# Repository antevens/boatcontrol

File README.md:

# Prototype, use at your own risk

# Boatcontrol

## About

Boatcontrol is an open hardware design for a marine grade SMART/IoT electrical
distribution panel and electronics platform (boat) controller.

It's an I/O breakout board capable of switching 32 onboard laching relays and
optionally 32 momentary/laching relays using addon boards switchnig  up to 60A
AC/DC 0-400V per circuit.

The "smart" part is provided by either a **Raspberry Pi** HAT or a
**Nvidia Jetson** (Nano/Xavier NX) either of which can be mounted on the board.

All critical parts are designed to be field serviceable, components using
through-holes are used where possible for better durability in mobile marine
environment. Note that these boards need to carry significant amounts of current
and high voltage and as such PCB thickness and clearances are CRITICAL along
with proper thermal management.

Special care has been taken to limit idle power consumption wherever possible, on
it's own the board will only consume 15 Milliwatts when idle, if a Raspberry Pi (RPi) Zero is
mated it will add 80-120 Milliwatts, a fully fledged RPi 4 with all the bells and
whistles will add up to 3.4 Watts, a Jetson Xavier NX will bring the total to
10-15 Watts depending on configuration. Jumpers are provided where applicable
to disable LEDs to reduce power consumption when idle. Each active indicator LED
will likely consume 10-20 Milliwatts. Note that using a momentary add-on board can increase
the power consumption substancially depending on which relays are used and how
much time they spend on the "ON" position.

Effort was taken to make the boards as reliable as possible and enable them to
be operated in emergencies and under failure conditions. All circuits can be
operated manually on the board as long as the board has a power source over 6v
and below 30v (see optional 12V vs 24V operation and PSU).
Operation using external 5V TTL inputs via the RJ45 connectors is
available regardless of the state or presence of the RPi/Jetson.

The board can be set to run in either 12V or 24V mode, for operation
over 13V please make sure the optional 12V PSU components are in place and
the appropriate solder jumpers bridged.
For 12V operation make sure the 12V bypass jumper/solder pads are bridged.

## PCB Stack & Manufacturing

The design includes a main board and (at the time of launch) two optional addon
boards, the primary board is designed for 4 layer 2.4-3.2mm PCBs with the following sizes/layers:

#### Main board - 536mm x 308mm (just over 21" x 12")
* Front Power, 6oz (220um) copper, min spacing 0.500mm)
* First Signal, 1oz (35um) copper, min spacing 0.250mm)
* Second Signal, 1oz (35um) copper, min spacing 0.250mm)
* Back Power, 6oz (220um) copper, min spacing 0.500mm)

#### Addon boards - 153mm x 106mm (just over 5" x 4")
* The high current daughter board is designed for 4 layer 1/13oz (35/450um) copper.
* The non-latching daughter board is designed for 4 layer 1/6oz (35/200um) copper.
* The non-existent current sensing daughter board .. will probably use 6oz copper.
* The non-existent Full ESD optocoupler/isolator board .. will probably use 1oz copper.

PCB Stack Thickness of daughter boards can vary as long as they are over 1mm

It's important that the power layers are on the outside for cooling purposes,
internal layers would require substantially thicker copper layers.

There aren't very many PCB manufacturers around that will/can produce a board
like this, especially in small quantities and the tooling fee will be a
substantial part of the total cost.

At the time of writing I would estimate at least $400 USD for tooling
setup and then $350 USD for each board manufactured. The manufacturers that
have online order forms for 4 layer heavy copper PCBs are:

* https://www.pcbcart.com
* https://www.pcbway.com
* https://pcbgogo.com

Note that these costs are only for the PCB, not for assembly or parts.

Note that a regular PCB panel is 457 x 610 (18" x 24"), each panel therefor can
acomidate 1 main board and 3 addon boards, consider this when ordering boards
and possibly create your own panel if your addon boards can use the same layer
stack as the primary board.

## Enclosure

Any reasonably sized enclosure will work but this board was designed to fit in
the **Fibox PC 5638 18T** (a custom mount plate will be needed since PCB standoffs don't
line up with the box attachment points).

This should give a rating of IP65/IK09

https://www.fibox.com/catalog/product/2393/2539557_ENG3.pdf

All cables should be installed with cable glands and drip loops, only install
cable glands on the bottom and optionally sides of the box, avoid making any
holes in the side facing up.

## Components, features and Bill of Materials

The components required to fully populate the board will typically cost around
{INSERT_BOM_COST}, here are full BOM carts from Mouser and DigiKey.

* {INSERT_LINK_TO_DIGIKEY}
* {INSERT_LINK_TO_MOUSER}

### Switches
Onboard switches can be momentary or locking depending on preference and application.
Typically one would use momentary switches for latching relays and locking
switches for non-latching relays.* For operating things like bilge pumps or
other devices that should only be turned on momentarily it might be beneficial
to use a non-latching relay with a momentary push button.

If for some reason locking switches are used with latching relays care must be
taken since most latching relay coils can't withstand being energized for long
periods and ideally should only be energized for less than a second*

The onboard switches are primarily for use in emergencies and debugging and while
they do provide protection against powering two coils in the same relay at the
same time they do not restrict the time a coil is energized unlike the RJ45 or
GPIO inputs.

All DPDT E3 series switches from Panasonic should work such as the ESB30 and ESB33
series, note that locking ESB30 switches can be converted to momentary
operation very easily even after soldering.

*The only exception to this would be if a user wants
to be able to physically disable a particular relay/circuit in which case two
locking relays can be used, if both of them are engaged at the same time they
will prevent all signals from reaching a latching relay behind them and at the
same time prevent each other from energizing the relay.

### Circuit breakers

The Schurter T9-818 breakers are  available in 3-15A current ratings and can
handle up to 48VDC and up to 240VAC.

The main board has a total of 32 breakers in 3 bank configurations, the board
can be outfitted with any configuration of breakers as long as the total does
not exceed 60A per bank or if a bank exceeds 60A then it should be protected by an
external 60A AC or DC breaker.

### The main (base) board layout includes sockets/circuits for:

#### 16 x 0-24V DC Common input channels/circuits:
* Input polarity protection and indicator LED
* Latching relay rated for 24V DC
* Thermally fused to 3A (can be swapped for 6A, 10A and 16A)
* Total current of these circuits should not exceed 60A

#### 8 x 0-24V DC Common input channels/circuits:
* Input polarity protection and indicator LED
* Latching relay rated for 24V DC
* 4 x thermally fused to 6A (can be swapped for 6A, 10A and 16A)
* 2 x thermally fused to 10A (can be swapped for 6A, 10A and 16A)
* 2 x thermally fused to 16A (can be swapped for 6A, 10A and 16A)
* Total current of these circuits should not exceed 60A

#### 8 x 100-250V AC Common input channels/circuits:
* AC Live/Neutral indicator LED
* Latching relay rated for 24V DC
* 4 x thermally fused to 6A (can be swapped for 6A, 10A and 16A)
* 2 x thermally fused to 10A (can be swapped for 6A, 10A and 16A)
* 2 x thermally fused to 16A (can be swapped for 6A, 10A and 16A)
* Total current of these circuits should not exceed 60A

## Addon boards
Addon boards connect to the main board using a 2 x 20 female pin header.
The main board male connectors are reversed compared to the GPIO header to avoid
confusion and prevent RPis or Jetson boards from being accidentally connected to
an addon-board header.

### Latching Relay Addon Board:
* 8 x 0-277V AC/DC Individual input/output channels/circuits
* Individual channel current should not exceed 60A
* No circuit breakers, polarity indicators or protection

### Momentary (Non Latching) Paired Addon Board:
* 16 (8 pairs*) x 12V DC non latching input/output channels/circuits
* Individual channel current should not exceed 32A
* No circuit breakers, polarity indicators or protection

_Non-latching Relays are paired and only one of a pair can be powered at any given time._

_All relays on a board share a common "Anode"/"Cathode", make sure to
adjust the solder-jumpers on the backside for the type of relays used so that
the relay polarity is correct. and that the correct driver array is chosen
(ULN2803A vs. TBD62783APG)_

Keep in mind that there is no requirement to fully populate the board and a partially
populated board is a great way to plan for future expansions given that the
board is field serviceable assuming the heavy copper soldering is done.

## Modes of operation
Each channel/circuit can be controlled using three different methods:

1. Using the onboard switches (these directly energize the relay coils)

2. Using two external switch signals wired up using CAT5/6 with RJ45
connectors. The signals use 5V TTL logic and are active HIGH.
The signals are filtered for noise and duration to protect the relays,
this ensures that only one coil can be energized at any given time and
only for a period of 1 second. Due to this filtering these can be safely
wired to 3-way "Latching" wall/panel switches or momentary push buttons.

3. Using I2C via the 2x20 Header, typically this would be done using a
Raspberry Pi (RPi) or Nvidia Jetson, for power efficiency consider using a RPi Zero.
See Node-Red source for IoT web based interfaces that can run on these platforms.

* Onboard bi-colour LEDs indicate coil energy state and pulses to "ON"/"OFF" coils.
* For latching relays RED indicates the circuit being turned ON while GREEN indicates the circuit being turned OFF.
* For non-latching relays RED and GREEN each represent a separate relay in a pair.

## Technical details

While the scale is disproportionate the main board is really just a rather large
Raspberry Pi HAT though it does not require an RPi to operate.
__Note that the board will act as a power supply for the RPi and Jetson
Nano eliminating the need for a separate PSU.__
__The Nvidia JetsonXavier products such as the NX and AGX will still need a separate (19V)
power source.__

All communication between the RPi and the board is done using I2C, this only
requires 2 pins/wires and makes it safe to use in combination with most if not all
other HATs. In particular it can co-exist with AIS and GPS hats like the dAISy though you
might want to run your chart-plotting or navigation software on a separate
RPi/Jetson NX and have a dedicated micro-computer for controlling your electrical system.

The Sailor Hat or PICAN-M HATs might be of particular interest to allow the
Boatcontrol board to act as an NMEA 0183/2000 or Seatalk device.

* https://hatlabs.fi/product-category/sh-rpi/sh-rpi-devices
* https://www.skpang.co.uk/collections/hats/products/pican-m-with-can-bus-micro-c-and-rs422-connector-3a-smps
* https://copperhilltech.com/pican-m-nmea-0183-nmea-2000-hat-for-raspberry-pi/

### RJ45 Connectors & Remote I/O
The top/right (J108) RJ45 connector is used to remotely control relays on the main
board. Each RJ45 socket controls 2 latching relays or 2 non-latching relay pairs (4).
Every socket consists of 4 separate 5V supply pins supplied via a 10KΩ resistor.

All J108 (top connector)inputs are ESD protected using clamp diodes in the
74HCT86 packs to the following standards:
* HBM JESD22-A114F exceeds 2000 V
* MM JESD22-A115-A exceeds 200 V

For long cable runs the resistor banks on the back can be replaced with lower
resistance values.

Half of the bottom/left (J107) RJ45 connector is used to remotely control addon
boards.

Each RJ45 socket can control 4 channels, typically controlling 2 latching relays
or 2 non-latching relay pairs (4).

**Note that for these connectors there are no current limiting resistors so
current is only limited by what the onboard PSU can supply and shorting this
can de-power the RPi/Jetson!**

**Pairing is important for all RJ45CAT5/6 wiring, it's highly
recommended that the source/sink to control each relay uses a twisted pair,
this will minimize loss and interference. Pairs are typically colored as shown here**

_Advanced uses may also include shielding but this is beyond the scope of this document._

#### 12V "High Voltage/Current" Pins
There are 16 extra IO pins that can provide up to 500mA each, this is provided
using an MCP23017 and a ULN2803* with a clamp diode. Examples of use cases would
be external relays, solenoids, small motors, high power LEDs, Cameras, etc.

_*can be substituted with a TBD62783APG to swap polarity from 12V source to GND
sink._

#### Raspberry Pi / Jetson  I/O
All pins from the GPIO header are made available via RJ45 to allow easy
expansion and remote mounting of devices such as GPS and AIS devices.

_Note that the 5V pins are shared with the RPi and maximum currents governed by
the RPi design not the Boatcontrol._

*_Note that no additional protection or filtering is provided, the pins are
simply mapped from the RPi GPIO header directly to RJ45 without any provision
to minimize signal degradation or distortion._

_Note that this includes the I2C bus which can be used to communicate directly
with all devices on the main and addon boards_

**IMPORTANT** - Since no extra ESD filtering or opto-isolaion is provided for
thes GPIO ports if there there is any chance of surges or high voltages these
should be isolated from the board using digital isolators or optocouplers
and transient voltage suppressors. For remote installations of the
Raspberry Pi/Jetson you might also want to add debounce and provide 3v from an
isolated source.

### RPi HAT / Jetson GPIO Interface
Using the GPIO header there are two ways to connect an RPi or Nvidia Jetson
device to the board.
1. Install female pin header on the Boatcontrol, mount the device directly in
the upside down position, if you choose this option make sure the particular board you are mounting has
enough clearance.*
2. Install a male pin header on the Boatcontrol, mount the device using a
   ribbon cable.

*While the RPi Zero is guaranteed to fit and with long headers all the
Pi/Pi2/Pi2/Pi4s should fit you should make sure your device fits before
choosing this mounting method.

_If using a Jetson Xavier NX or AGX make sure you use the horizontal inductors for the
PSU since the vertical arrangement can block one of the mounting holes._

### Addon cards

### I2C interface and addresses
The I2C addresses of the IO Expanders can be modified* using solder jumpers on
the backside of the PCB but the defaults are:

    0x20 (32) 3A Common Input DC #1-8
    0x21 (33) 3A Common Input DC #9-16
    0x22 (34) 6/10/16A Common Input DC
    0x23 (35) 6/10/16A Common Input AC
    0x24 (36) 60A Individual AC/DC
    0x25 (37) Additional IO #1 to RJ45 Cat5/6
    0x26 (38) Additional IO #2 to RJ45 Cat5/6

*Bring plenty of watts, it's a 6oz PCB!

# Software
One of the primary advantages of having the GPIO interface and using a
Raspberry Pi or Nvidia Jetson to interface with the board is the simplicity and
ease of use allowing each installation to be customized for the particular boat
and users, changes can be made in real-time using a web browser and all the
functionality and features are accessible from any web enabled device onboard
or remote.

The following are screenshots from development UIs used to debug and test the
hardware, they show some of the functionality that's possible including
day/night views, automated alerts and functionality.

This particular interface is built using Node-Red and is running on an RPi 4.

# Open Hardware

Feel free to modify this to suit your own needs or have it made as it's
currently configured. Be careful when upgrading circuit breakers to not exceed the
current/thermal capacity of the board. If you use thinner copper than 6oz make
sure to appropriately downgrade the thermal breakers to reduce maximum current.

## Bus bars, jumper wires and 2 layer boards

Depending on where you live and your requirements it might make more sense
for you to use laser cut copper bus bars or solder wires on the back of your PCB to
avoid the expensive 6oz copper layers.

The PCB was architected to facilitate 1oz / 2 layer construction, there is a
git branch called [2layer](../../tree/2layers) which is the last version supporting 2 layers. *In
theory* this could be made with 1oz copper and used with bus bars or jumper
wires but it's not been kept up to date. Let me know if you want to use this
and we can probably work together to merge relevant changes.

## Key design decisions and parameters

* All critical components are through-hole for field maintenance on moving platforms and secure attachment for vibration and G loads.
* All relays can be controlled from either the RPi/Nvidia or using analog control signals via RJ45/CAT5/6 connectors/cables.
* All onboard relays are latching dual coil with individual control circuits.
* All analog input channels have pulse generators for the relays to protect them from overheating.
* Built-in high efficiency 5/12v step down converters to power the RPi/Nano and logic components and supply current for analog control.
* 8x 3-16A 250V AC shared bus protected circuits
* 24x 3-16A 12-24V DC shared bus protected circuits
* 32x 12-24V 500mA DC Logic/Relay breakout via RJ45
* Optional 16x 250V AC non-latching unprotected add-on board
* Optional 8x 60A 277V AC latching individual unprotected add-on board
* All onboard DC channels are polarity protected with high efficiency PFETs
* Protection is provided using thermal circuit breakers, the permitted amperage can be changed by switching out breakers, no breakers are provided for the 60A circuits, suggest using external breakers.

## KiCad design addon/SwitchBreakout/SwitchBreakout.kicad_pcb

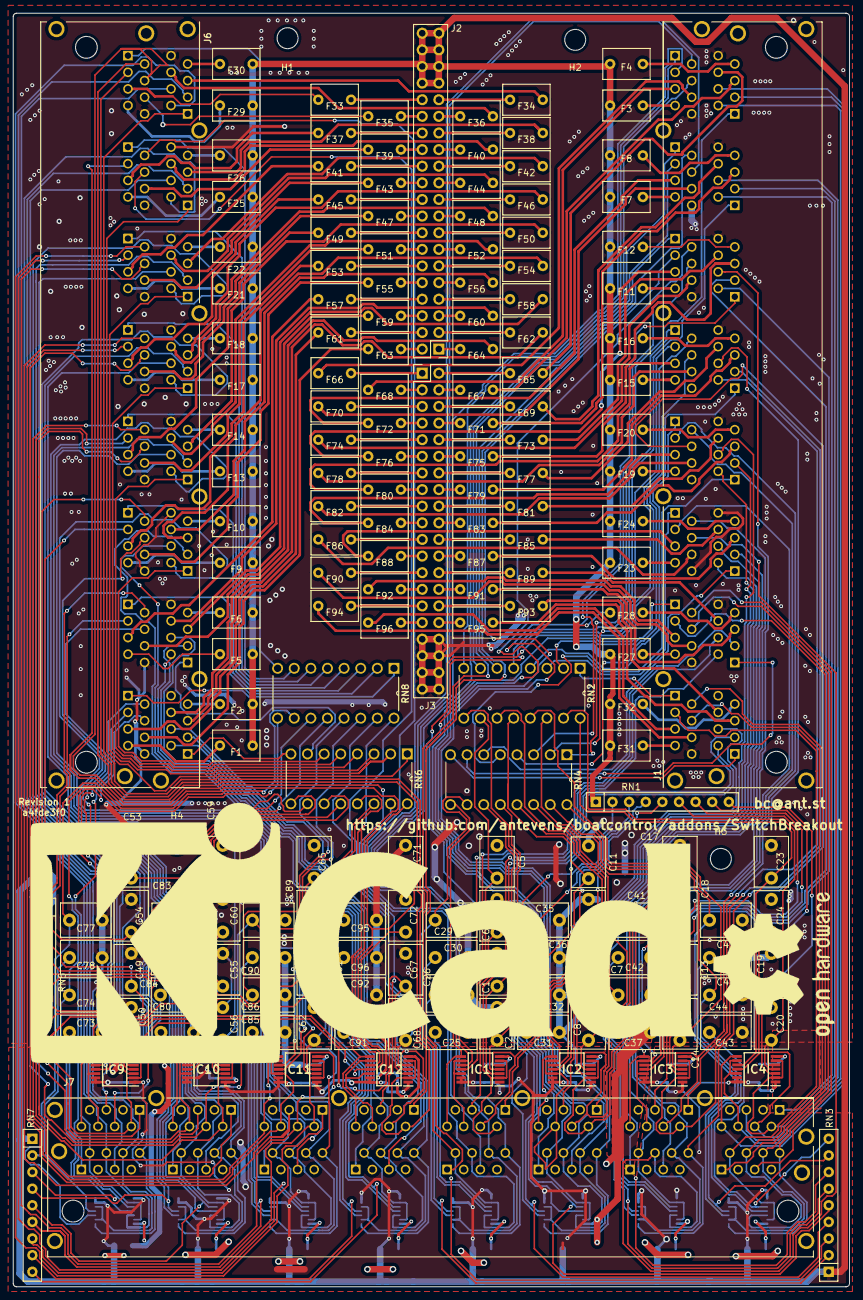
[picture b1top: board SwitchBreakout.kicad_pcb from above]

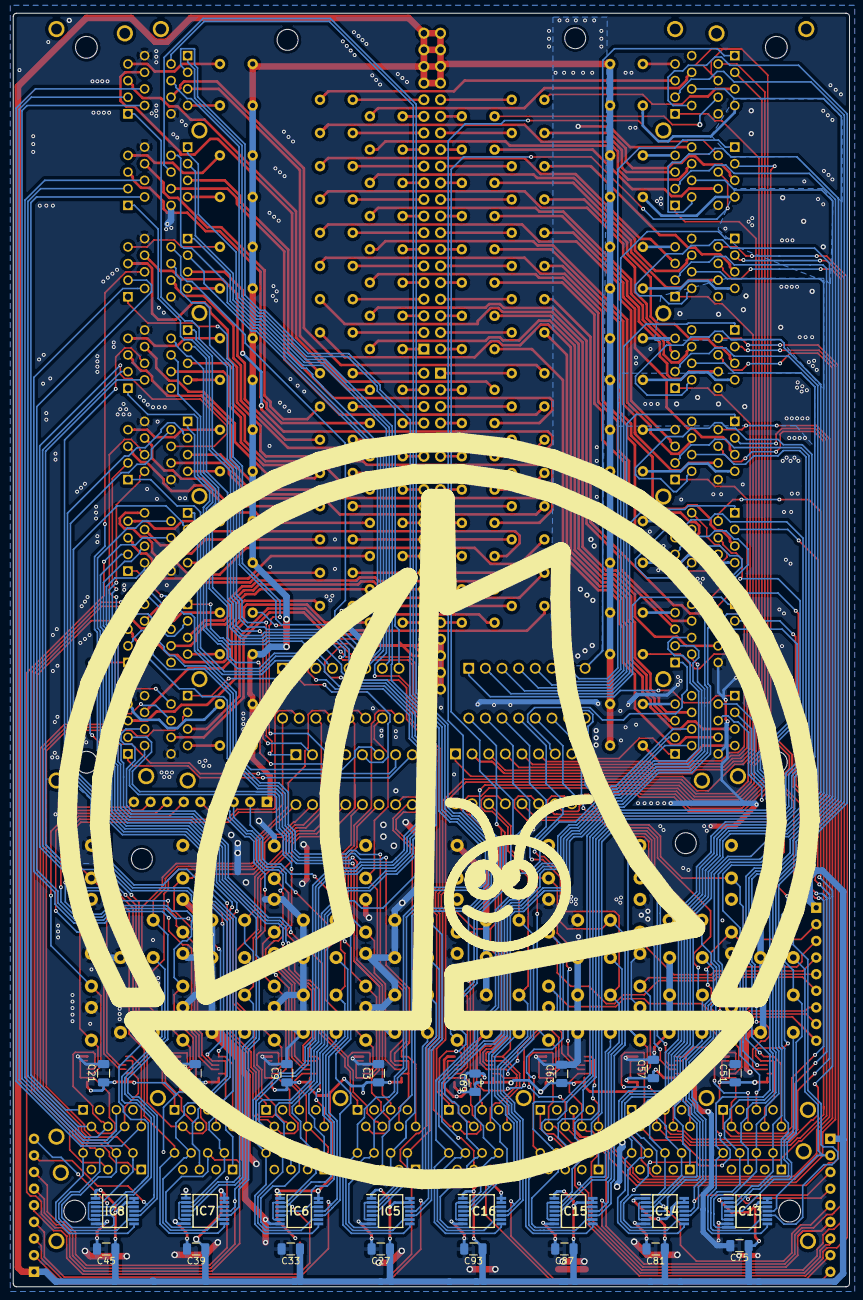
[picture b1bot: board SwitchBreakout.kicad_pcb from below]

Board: 2 copper layers, 127.8 x 194.6 mm, 213 parts (26 on the bottom side), 354 nets.

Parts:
C1, C2, C5, C6, C7, C8, C11, C12, C13, C14, C17, C18, C19, C20, C23, C24, C25, C26, C29, C30, C31, C32, C35, C36, C37, C38, C41, C42, C43, C44, C47, C48, C49, C50, C53, C54, C55, C56, C59, C60, C61, C62, C65, C66, C67, C68, C71, C72, C73, C74, C77, C78, C79, C80, C83, C84, C85, C86, C89, C90, C91, C92, C95, C96: 1uF; C_Disc_D7.5mm_W5.0mm_P5.00mm
C3, C9, C15, C21, C27, C33, C39, C45, C51, C57, C63, C69, C75, C81, C87, C93: 0.1uF; C_1206_3216Metric
F1, F2, F3, F4, F5, F6, F7, F8, F9, F10, F11, F12, F13, F14, F15, F16, F17, F18, F19, F20, F21, F22, F23, F24, F25, F26, F27, F28, F29, F30, F31, F32, F33, F34, F35, F36, F37, F38, F39, F40, F41, F42, F43, F44, F45, F46, F47, F48, F49, F50, F51, F52, F53, F54, F55, F56, F57, F58, F59, F60, F61, F62, F63, F64, F65, F66, F67, F68, F69, F70, F71, F72, F73, F74, F75, F76, F77, F78, F79, F80, F81, F82, F83, F84, F85, F86, F87, F88, F89, F90, F91, F92, F93, F94, F95, F96: Polyfuse; C_Rect_L7.0mm_W4.5mm_P5.00mm
G1: LOGO_ANT; Ant_Logo_SilkScreen
G2: LOGO_RUGLUDALLUR; Rugludallur-Logo_SilkScreen
H1, H2, H3, H4: MountingHole; MountingHole_3.2mm_M3
IC1, IC2, IC3, IC4, IC5, IC6, IC7, IC8, IC9, IC10, IC11, IC12, IC13, IC14, IC15, IC16: SN74HCS72QPWRQ1; SOP65P640X120-14N
J1, J6, J7: SS73100-047F; STEWART_SS73100-047F
J2, J3: Conn_02x20_Odd_Even; PinHeader_2x20_P2.54mm_Vertical
LOGO1: Logo_Open_Hardware_Large; OSHW-Logo2_24.3x20mm_SilkScreen
LOGO2: Logo_Open_Hardware_Large; KiCad-Logo_40mm_SilkScreen
RN1, RN3, RN5, RN7: 100KΩ; R_Array_SIP9
RN2, RN4, RN6, RN8: 1KΩ; DIP254P762X432-16P

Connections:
/A1: J1.A_2, J7.P_1
/A2: IC8.2, IC8.6, J1.A_3, J7.P_2
/A4: IC8.5, J1.A_4, J7.P_4
/A5: J1.B_2, J7.P_5
/A6: IC8.9, IC8.12, J1.B_3, J7.P_6
/A8: IC8.8, J1.B_4, J7.P_8
/B1: J1.C_2, J7.O_1
/B2: IC7.2, IC7.6, J1.C_3, J7.O_2
/B4: IC7.5, J1.C_4, J7.O_4
/B5: J1.D_2, J7.O_5
/B6: IC7.9, IC7.12, J1.D_3, J7.O_6
/B8: IC7.8, J1.D_4, J7.O_8
/C1: J1.E_2, J7.N_1
/C2: IC6.2, IC6.6, J1.E_3, J7.N_2
/C4: IC6.5, J1.E_4, J7.N_4
/C5: J1.F_2, J7.N_5
/C6: IC6.9, IC6.12, J1.F_3, J7.N_6
/C8: IC6.8, J1.F_4, J7.N_8
/D1: J1.G_2, J7.M_1
/D2: IC5.2, IC5.6, J1.G_3, J7.M_2
/D4: IC5.5, J1.G_4, J7.M_4
/D5: J1.H_2, J7.M_5
/D6: IC5.9, IC5.12, J1.H_3, J7.M_6
/D8: IC5.8, J1.H_4, J7.M_8
/D-Lach 9-16/BTN1: J1.I_1, RN4.8
/D-Lach 9-16/BTN2: J1.J_1, RN4.7
/D-Lach 9-16/BTN3: J1.K_1, RN4.6
/D-Lach 9-16/BTN4: J1.L_1, RN4.5
/D-Lach 9-16/BTN5: J1.M_1, RN4.4
/D-Lach 9-16/BTN6: J1.N_1, RN4.3
/D-Lach 9-16/BTN7: J1.O_1, RN4.2
/D-Lach 9-16/BTN8: J1.P_1, RN4.1
/D-Lach 9-16/D-Latch 0/BTN1: C26.2, IC5.4, RN4.9
/D-Lach 9-16/D-Latch 0/BTN2: C29.2, IC5.10, RN4.10
/D-Lach 9-16/D-Latch 0/CLK1: C25.2, IC5.3, RN3.3
/D-Lach 9-16/D-Latch 0/CLK2: C30.2, IC5.11, RN3.2
/D-Lach 9-16/D-Latch 1/BTN1: C32.2, IC6.4, RN4.11
/D-Lach 9-16/D-Latch 1/BTN2: C35.2, IC6.10, RN4.12
/D-Lach 9-16/D-Latch 1/CLK1: C31.2, IC6.3, RN3.5
/D-Lach 9-16/D-Latch 1/CLK2: C36.2, IC6.11, RN3.4
/D-Lach 9-16/D-Latch 2/BTN1: C38.2, IC7.4, RN4.13
/D-Lach 9-16/D-Latch 2/BTN2: C41.2, IC7.10, RN4.14
/D-Lach 9-16/D-Latch 2/CLK1: C37.2, IC7.3, RN3.7
/D-Lach 9-16/D-Latch 2/CLK2: C42.2, IC7.11, RN3.6
/D-Lach 9-16/D-Latch 4/BTN1: C44.2, IC8.4, RN4.15
/D-Lach 9-16/D-Latch 4/BTN2: C47.2, IC8.10, RN4.16
/D-Lach 9-16/D-Latch 4/CLK1: C43.2, IC8.3, RN3.9
/D-Lach 9-16/D-Latch 4/CLK2: C48.2, IC8.11, RN3.8
/D-Latch 1-8/BTN1: J1.H_1, RN2.8
/D-Latch 1-8/BTN2: J1.G_1, RN2.7
/D-Latch 1-8/BTN3: J1.F_1, RN2.6
/D-Latch 1-8/BTN4: J1.E_1, RN2.5
/D-Latch 1-8/BTN5: J1.D_1, RN2.4
/D-Latch 1-8/BTN6: J1.C_1, RN2.3
/D-Latch 1-8/BTN7: J1.B_1, RN2.2
/D-Latch 1-8/BTN8: J1.A_1, RN2.1
/D-Latch 1-8/D-Latch 0/BTN1: C2.2, IC1.4, RN2.9
/D-Latch 1-8/D-Latch 0/BTN2: C5.2, IC1.10, RN2.10
/D-Latch 1-8/D-Latch 0/CLK1: C1.2, IC1.3, RN1.3
/D-Latch 1-8/D-Latch 0/CLK2: C6.2, IC1.11, RN1.2
/D-Latch 1-8/D-Latch 1/BTN1: C8.2, IC2.4, RN2.11
/D-Latch 1-8/D-Latch 1/BTN2: C11.2, IC2.10, RN2.12
/D-Latch 1-8/D-Latch 1/CLK1: C7.2, IC2.3, RN1.5
/D-Latch 1-8/D-Latch 1/CLK2: C12.2, IC2.11, RN1.4
/D-Latch 1-8/D-Latch 2/BTN1: C14.2, IC3.4, RN2.13
/D-Latch 1-8/D-Latch 2/BTN2: C17.2, IC3.10, RN2.14
/D-Latch 1-8/D-Latch 2/CLK1: C13.2, IC3.3, RN1.7
/D-Latch 1-8/D-Latch 2/CLK2: C18.2, IC3.11, RN1.6
/D-Latch 1-8/D-Latch 4/BTN1: C20.2, IC4.4, RN2.15
/D-Latch 1-8/D-Latch 4/BTN2: C23.2, IC4.10, RN2.16
/D-Latch 1-8/D-Latch 4/CLK1: C19.2, IC4.3, RN1.9
/D-Latch 1-8/D-Latch 4/CLK2: C24.2, IC4.11, RN1.8
/D-Latch 17-24/BTN1: J6.H_1, RN6.8
/D-Latch 17-24/BTN2: J6.G_1, RN6.7
/D-Latch 17-24/BTN3: J6.F_1, RN6.6
/D-Latch 17-24/BTN4: J6.E_1, RN6.5
/D-Latch 17-24/BTN5: J6.D_1, RN6.4
/D-Latch 17-24/BTN6: J6.C_1, RN6.3
/D-Latch 17-24/BTN7: J6.B_1, RN6.2
/D-Latch 17-24/BTN8: J6.A_1, RN6.1
/D-Latch 17-24/D-Latch 0/BTN1: C50.2, IC9.4, RN6.9
/D-Latch 17-24/D-Latch 0/BTN2: C53.2, IC9.10, RN6.10
/D-Latch 17-24/D-Latch 0/CLK1: C49.2, IC9.3, RN5.3
/D-Latch 17-24/D-Latch 0/CLK2: C54.2, IC9.11, RN5.2
/D-Latch 17-24/D-Latch 1/BTN1: C56.2, IC10.4, RN6.11
/D-Latch 17-24/D-Latch 1/BTN2: C59.2, IC10.10, RN6.12
/D-Latch 17-24/D-Latch 1/CLK1: C55.2, IC10.3, RN5.5
/D-Latch 17-24/D-Latch 1/CLK2: C60.2, IC10.11, RN5.4
/D-Latch 17-24/D-Latch 2/BTN1: C62.2, IC11.4, RN6.13
/D-Latch 17-24/D-Latch 2/BTN2: C65.2, IC11.10, RN6.14
/D-Latch 17-24/D-Latch 2/CLK1: C61.2, IC11.3, RN5.7
/D-Latch 17-24/D-Latch 2/CLK2: C66.2, IC11.11, RN5.6
/D-Latch 17-24/D-Latch 4/BTN1: C68.2, IC12.4, RN6.15
/D-Latch 17-24/D-Latch 4/BTN2: C71.2, IC12.10, RN6.16
/D-Latch 17-24/D-Latch 4/CLK1: C67.2, IC12.3, RN5.9
/D-Latch 17-24/D-Latch 4/CLK2: C72.2, IC12.11, RN5.8
/D-Latch 25-32/BTN1: J6.I_1, RN8.8
/D-Latch 25-32/BTN2: J6.J_1, RN8.7
/D-Latch 25-32/BTN3: J6.K_1, RN8.6
/D-Latch 25-32/BTN4: J6.L_1, RN8.5
/D-Latch 25-32/BTN5: J6.M_1, RN8.4
/D-Latch 25-32/BTN6: J6.N_1, RN8.3
/D-Latch 25-32/BTN7: J6.O_1, RN8.2
/D-Latch 25-32/BTN8: J6.P_1, RN8.1
/D-Latch 25-32/D-Latch 0/BTN1: C74.2, IC13.4, RN8.9
/D-Latch 25-32/D-Latch 0/BTN2: C77.2, IC13.10, RN8.10
/D-Latch 25-32/D-Latch 0/CLK1: C73.2, IC13.3, RN7.3
/D-Latch 25-32/D-Latch 0/CLK2: C78.2, IC13.11, RN7.2
/D-Latch 25-32/D-Latch 1/BTN1: C80.2, IC14.4, RN8.11
/D-Latch 25-32/D-Latch 1/BTN2: C83.2, IC14.10, RN8.12
/D-Latch 25-32/D-Latch 1/CLK1: C79.2, IC14.3, RN7.5
/D-Latch 25-32/D-Latch 1/CLK2: C84.2, IC14.11, RN7.4
/D-Latch 25-32/D-Latch 2/BTN1: C86.2, IC15.4, RN8.13
/D-Latch 25-32/D-Latch 2/BTN2: C89.2, IC15.10, RN8.14
/D-Latch 25-32/D-Latch 2/CLK1: C85.2, IC15.3, RN7.7
/D-Latch 25-32/D-Latch 2/CLK2: C90.2, IC15.11, RN7.6
/D-Latch 25-32/D-Latch 4/BTN1: C92.2, IC16.4, RN8.15
/D-Latch 25-32/D-Latch 4/BTN2: C95.2, IC16.10, RN8.16
/D-Latch 25-32/D-Latch 4/CLK1: C91.2, IC16.3, RN7.9
/D-Latch 25-32/D-Latch 4/CLK2: C96.2, IC16.11, RN7.8
/E1: J1.I_2, J7.E_1
/E2: IC1.2, IC1.6, J1.I_3, J7.E_2
/E4: IC1.5, J1.I_4, J7.E_4
/E5: J1.J_2, J7.E_5
/E6: IC1.9, IC1.12, J1.J_3, J7.E_6
/E8: IC1.8, J1.J_4, J7.E_8
/F1: J1.K_2, J7.F_1
/F2: IC2.2, IC2.6, J1.K_3, J7.F_2
/F4: IC2.5, J1.K_4, J7.F_4
/F5: J1.L_2, J7.F_5
/F6: IC2.9, IC2.12, J1.L_3, J7.F_6
/F8: IC2.8, J1.L_4, J7.F_8
/G1: J1.M_2, J7.G_1
/G2: IC3.2, IC3.6, J1.M_3, J7.G_2
/G4: IC3.5, J1.M_4, J7.G_4
/G5: J1.N_2, J7.G_5
/G6: IC3.9, IC3.12, J1.N_3, J7.G_6
/G8: IC3.8, J1.N_4, J7.G_8
/H1: J1.O_2, J7.H_1
/H2: IC4.2, IC4.6, J1.O_3, J7.H_2
/H4: IC4.5, J1.O_4, J7.H_4
/H5: J1.P_2, J7.H_5
/H6: IC4.9, IC4.12, J1.P_3, J7.H_6
/H8: IC4.8, J1.P_4, J7.H_8
/I1: J6.A_2, J7.I_1
/I2: IC13.2, IC13.6, J6.A_3, J7.I_2
/I4: IC13.5, J6.A_4, J7.I_4
/I5: J6.B_2, J7.I_5
/I6: IC13.9, IC13.12, J6.B_3, J7.I_6
/I8: IC13.8, J6.B_4, J7.I_8
/J1: J6.C_2, J7.J_1
/J2: IC14.2, IC14.6, J6.C_3, J7.J_2
/J4: IC14.5, J6.C_4, J7.J_4
/J5: J6.D_2, J7.J_5
/J6: IC14.9, IC14.12, J6.D_3, J7.J_6
/J8: IC14.8, J6.D_4, J7.J_8
/K1: J6.E_2, J7.K_1
/K2: IC15.2, IC15.6, J6.E_3, J7.K_2
/K4: IC15.5, J6.E_4, J7.K_4
/K5: J6.F_2, J7.K_5
/K6: IC15.9, IC15.12, J6.F_3, J7.K_6
/K8: IC15.8, J6.F_4, J7.K_8
/L1: J6.G_2, J7.L_1
/L2: IC16.2, IC16.6, J6.G_3, J7.L_2
/L4: IC16.5, J6.G_4, J7.L_4
/L5: J6.H_2, J7.L_5
/L6: IC16.9, IC16.12, J6.H_3, J7.L_6
/L8: IC16.8, J6.H_4, J7.L_8
/M1: J6.I_2, J7.D_1
/M2: IC12.2, IC12.6, J6.I_3, J7.D_2
/M4: IC12.5, J6.I_4, J7.D_4
/M5: J6.J_2, J7.D_5
/M6: IC12.9, IC12.12, J6.J_3, J7.D_6
/M8: IC12.8, J6.J_4, J7.D_8
/N1: J6.K_2, J7.C_1
/N2: IC11.2, IC11.6, J6.K_3, J7.C_2
/N4: IC11.5, J6.K_4, J7.C_4
/N5: J6.L_2, J7.C_5
/N6: IC11.9, IC11.12, J6.L_3, J7.C_6
/N8: IC11.8, J6.L_4, J7.C_8
/O1: J6.M_2, J7.B_1
/O2: IC10.2, IC10.6, J6.M_3, J7.B_2
/O4: IC10.5, J6.M_4, J7.B_4
/O5: J6.N_2, J7.B_5
/O6: IC10.9, IC10.12, J6.N_3, J7.B_6
/O8: IC10.8, J6.N_4, J7.B_8
/P1: J6.O_2, J7.A_1
/P2: IC9.2, IC9.6, J6.O_3, J7.A_2
/P4: IC9.5, J6.O_4, J7.A_4
/P5: J6.P_2, J7.A_5
/P6: IC9.9, IC9.12, J6.P_3, J7.A_6
/P8: IC9.8, J6.P_4, J7.A_8
GND: C1.1, C2.1, C3.2, C5.1, C6.1, C7.1, C8.1, C9.2, C11.1, C12.1, C13.1, C14.1, C15.2, C17.1, C18.1, C19.1, C20.1, C21.2, C23.1, C24.1, C25.1, C26.1, C27.2, C29.1, C30.1, C31.1, C32.1, C33.2, C35.1, C36.1, C37.1, C38.1, C39.2, C41.1, C42.1, C43.1, C44.1, C45.2, C47.1, C48.1, C49.1, C50.1, C51.2, C53.1, C54.1, C55.1, C56.1, C57.2, C59.1, C60.1, C61.1, C62.1, C63.2, C65.1, C66.1, C67.1, C68.1, C69.2, C71.1, C72.1, C73.1, C74.1, C75.2, C77.1, C78.1, C79.1, C80.1, C81.2, C83.1, C84.1, C85.1, C86.1, C87.2, C89.1, C90.1, C91.1, C92.1, C93.2, C95.1, C96.1, IC1.7, IC2.7, IC3.7, IC4.7, IC5.7, IC6.7, IC7.7, IC8.7, IC9.7, IC10.7, IC11.7, IC12.7, IC13.7, IC14.7, IC15.7, IC16.7, J1.A_8, J1.B_8, J1.C_8, J1.D_8, J1.E_8, J1.F_8, J1.G_8, J1.H_8, J1.I_8, J1.J_8, J1.K_8, J1.L_8, J1.M_8, J1.N_8, J1.O_8, J1.P_8, J3.33, J3.34, J3.35, J3.36, J3.37, J3.38, J3.39, J3.40, J6.A_8, J6.B_8, J6.C_8, J6.D_8, J6.E_8, J6.F_8, J6.G_8, J6.H_8, J6.I_8, J6.J_8, J6.K_8, J6.L_8, J6.M_8, J6.N_8, J6.O_8, J6.P_8
unnamed: F1.2, J6.P_7
unnamed: F2.2, J6.H_7
unnamed: F3.2, J1.H_7
unnamed: F4.2, J1.P_7
unnamed: F5.2, J6.O_7
unnamed: F6.2, J6.G_7
unnamed: F7.2, J1.G_7
unnamed: F8.2, J1.O_7
unnamed: F9.2, J6.N_7
unnamed: F10.2, J6.F_7
unnamed: F11.2, J1.F_7
unnamed: F12.2, J1.N_7
unnamed: F13.2, J6.M_7
unnamed: F14.2, J6.E_7
unnamed: F15.2, J1.E_7
unnamed: F16.2, J1.M_7
unnamed: F17.2, J6.L_7
unnamed: F18.2, J6.D_7
unnamed: F19.2, J1.D_7
unnamed: F20.2, J1.L_7
unnamed: F21.2, J6.K_7
unnamed: F22.2, J6.C_7
unnamed: F23.2, J1.C_7
unnamed: F24.2, J1.K_7
unnamed: F25.2, J6.J_7
unnamed: F26.2, J6.B_7
unnamed: F27.2, J1.B_7
unnamed: F28.2, J1.J_7
unnamed: F29.2, J6.I_7
unnamed: F30.2, J6.A_7
unnamed: F31.2, J1.A_7
unnamed: F32.2, J1.I_7
unnamed: F33.1, J6.I_5
unnamed: F33.2, J2.32
unnamed: F34.1, J6.A_5
unnamed: F34.2, J2.31
unnamed: F35.1, J6.I_6
unnamed: F35.2, J2.30
unnamed: F36.1, J6.A_6
unnamed: F36.2, J2.29
unnamed: F37.1, J6.J_5
unnamed: F37.2, J2.28
unnamed: F38.1, J6.B_5
unnamed: F38.2, J2.27
unnamed: F39.1, J6.J_6
unnamed: F39.2, J2.26
unnamed: F40.1, J6.B_6
unnamed: F40.2, J2.25
unnamed: F41.1, J6.K_5
unnamed: F41.2, J2.24
unnamed: F42.1, J6.C_5
unnamed: F42.2, J2.23
unnamed: F43.1, J6.K_6
unnamed: F43.2, J2.22
unnamed: F44.1, J6.C_6
unnamed: F44.2, J2.21
unnamed: F45.1, J6.L_5
unnamed: F45.2, J2.20
unnamed: F46.1, J6.D_5
unnamed: F46.2, J2.19
unnamed: F47.1, J6.L_6
unnamed: F47.2, J2.18
unnamed: F48.1, J6.D_6
unnamed: F48.2, J2.17
unnamed: F49.1, J6.M_5
unnamed: F49.2, J2.16
unnamed: F50.1, J6.E_5
unnamed: F50.2, J2.15
unnamed: F51.1, J6.M_6
unnamed: F51.2, J2.14
unnamed: F52.1, J6.E_6
unnamed: F52.2, J2.13
unnamed: F53.1, J6.N_5
unnamed: F53.2, J2.12
unnamed: F54.1, J6.F_5
unnamed: F54.2, J2.11
unnamed: F55.1, J6.N_6
unnamed: F55.2, J2.10
unnamed: F56.1, J6.F_6
unnamed: F56.2, J2.9
unnamed: F57.1, J6.O_5
unnamed: F57.2, J2.8
unnamed: F58.1, J6.G_5
unnamed: F58.2, J2.7
unnamed: F59.1, J6.O_6
unnamed: F59.2, J2.6
unnamed: F60.1, J6.G_6
unnamed: F60.2, J2.5
unnamed: F61.1, J6.P_5
unnamed: F61.2, J2.4
unnamed: F62.1, J6.H_5
unnamed: F62.2, J2.3
unnamed: F63.1, J6.P_6
unnamed: F63.2, J2.2
unnamed: F64.1, J6.H_6
unnamed: F64.2, J2.1
unnamed: F65.1, J1.P_6
unnamed: F65.2, J3.2
unnamed: F66.1, J1.H_6
unnamed: F66.2, J3.1
unnamed: F67.1, J1.P_5
unnamed: F67.2, J3.4
unnamed: F68.1, J1.H_5
unnamed: F68.2, J3.3
unnamed: F69.1, J1.O_6
unnamed: F69.2, J3.6
unnamed: F70.1, J1.G_6
unnamed: F70.2, J3.5
unnamed: F71.1, J1.O_5
unnamed: F71.2, J3.8
unnamed: F72.1, J1.G_5
unnamed: F72.2, J3.7
unnamed: F73.1, J1.N_6
unnamed: F73.2, J3.10
unnamed: F74.1, J1.F_6
unnamed: F74.2, J3.9
unnamed: F75.1, J1.N_5
unnamed: F75.2, J3.12
unnamed: F76.1, J1.F_5
unnamed: F76.2, J3.11
unnamed: F77.1, J1.M_6
unnamed: F77.2, J3.14
unnamed: F78.1, J1.E_6
unnamed: F78.2, J3.13
unnamed: F79.1, J1.M_5
unnamed: F79.2, J3.16
unnamed: F80.1, J1.E_5
unnamed: F80.2, J3.15
unnamed: F81.1, J1.L_6
unnamed: F81.2, J3.18
unnamed: F82.1, J1.D_6
unnamed: F82.2, J3.17
unnamed: F83.1, J1.L_5
unnamed: F83.2, J3.20
unnamed: F84.1, J1.D_5
unnamed: F84.2, J3.19
unnamed: F85.1, J1.K_6
unnamed: F85.2, J3.22
unnamed: F86.1, J1.C_6
unnamed: F86.2, J3.21
unnamed: F87.1, J1.K_5
unnamed: F87.2, J3.24
unnamed: F88.1, J1.C_5
unnamed: F88.2, J3.23
unnamed: F89.1, J1.J_6
unnamed: F89.2, J3.26
unnamed: F90.1, J1.B_6
unnamed: F90.2, J3.25
unnamed: F91.1, J1.J_5
unnamed: F91.2, J3.28
unnamed: F92.1, J1.B_5
unnamed: F92.2, J3.27
unnamed: F93.1, J1.I_6
unnamed: F93.2, J3.30
unnamed: F94.1, J1.A_6
unnamed: F94.2, J3.29
unnamed: F95.1, J1.I_5
unnamed: F95.2, J3.32
unnamed: F96.1, J1.A_5
unnamed: F96.2, J3.31
VCC: C3.1, C9.1, C15.1, C21.1, C27.1, C33.1, C39.1, C45.1, C51.1, C57.1, C63.1, C69.1, C75.1, C81.1, C87.1, C93.1, F1.1, F2.1, F3.1, F4.1, F5.1, F6.1, F7.1, F8.1, F9.1, F10.1, F11.1, F12.1, F13.1, F14.1, F15.1, F16.1, F17.1, F18.1, F19.1, F20.1, F21.1, F22.1, F23.1, F24.1, F25.1, F26.1, F27.1, F28.1, F29.1, F30.1, F31.1, F32.1, IC1.1, IC1.13, IC1.14, IC2.1, IC2.13, IC2.14, IC3.1, IC3.13, IC3.14, IC4.1, IC4.13, IC4.14, IC5.1, IC5.13, IC5.14, IC6.1, IC6.13, IC6.14, IC7.1, IC7.13, IC7.14, IC8.1, IC8.13, IC8.14, IC9.1, IC9.13, IC9.14, IC10.1, IC10.13, IC10.14, IC11.1, IC11.13, IC11.14, IC12.1, IC12.13, IC12.14, IC13.1, IC13.13, IC13.14, IC14.1, IC14.13, IC14.14, IC15.1, IC15.13, IC15.14, IC16.1, IC16.13, IC16.14, J2.33, J2.34, J2.35, J2.36, J2.37, J2.38, J2.39, J2.40, RN1.1, RN3.1, RN5.1, RN7.1

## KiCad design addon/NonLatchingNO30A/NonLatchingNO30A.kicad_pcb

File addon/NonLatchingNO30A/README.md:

Addon board for Boatcontrol 32.

The Boatcontrol 32 is a smart distribution panel and electrical system for on/off-grid and hybrid backup power systems that need to handle 12-24v DC 110-115v AC and 200-250V AC systems.
A perfect companion to a SMA Sunny Island or Sunny Boy Storage, Fronius or other battery inverters.

It's a one stop PCB that allows a Raspberry Pi (RPi) or Nvidia Jetson to control your entire electrical system while retaining full analog control from external switches and allowing manual override onboard in case of emergencies.
This addon board adds 16 x 30A AC/DC relays.

Note that the relays are paired for manual override. When operating relayes in
emergency mode only one out of a pair can be operated at a time.

https://github.com/antevens/boatcontrol/tree/master/addon/CommonCathode30A

BoatControl
https://github.com/antevens/boatcontrol

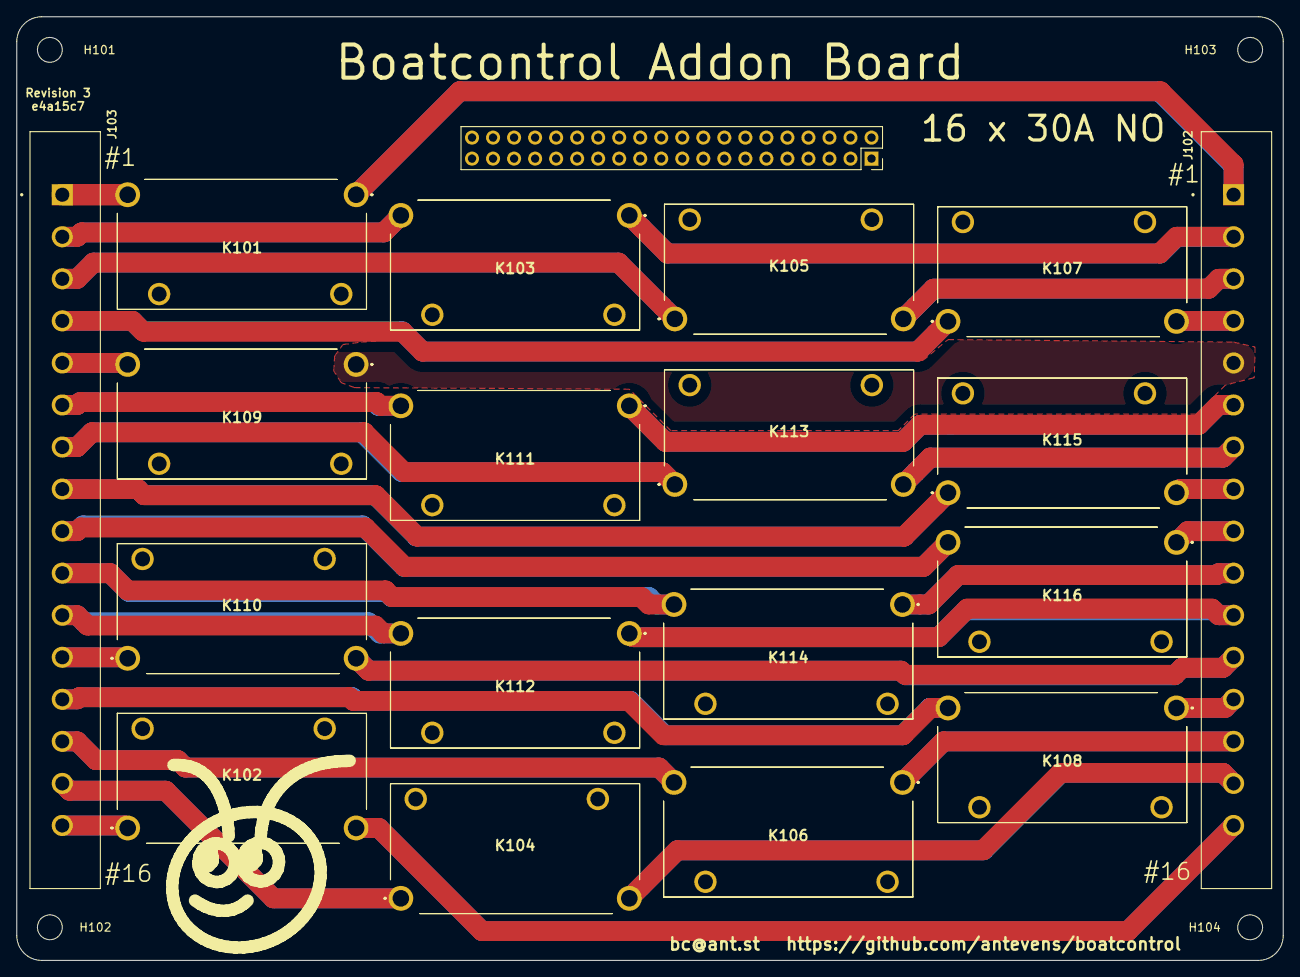
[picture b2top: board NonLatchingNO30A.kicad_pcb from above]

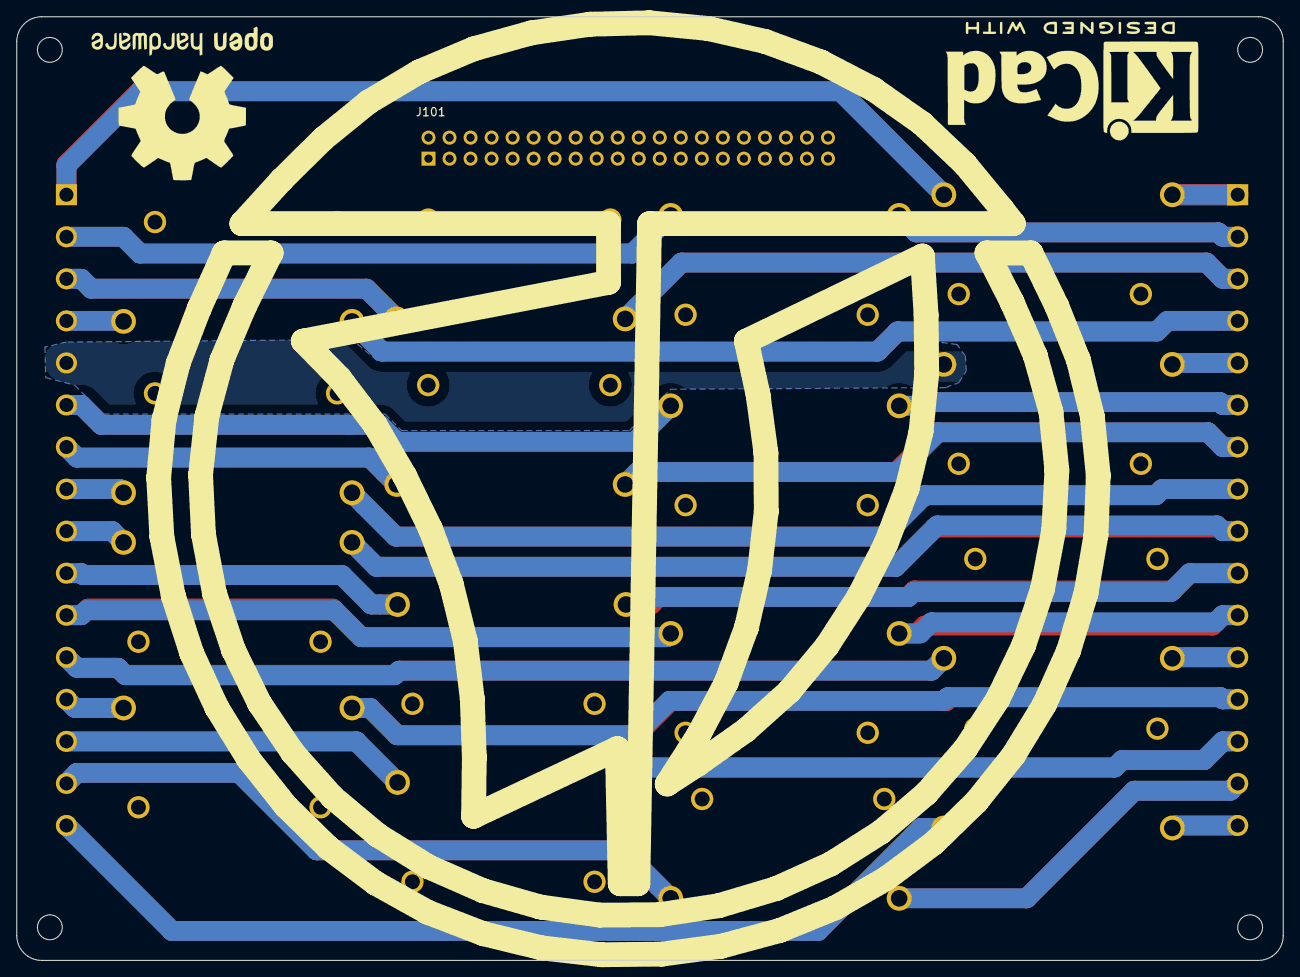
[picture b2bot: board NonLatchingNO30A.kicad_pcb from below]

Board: 4 copper layers, 153.0 x 114.0 mm, 27 parts (3 on the bottom side), 49 nets.

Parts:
G101: LOGO_RUGLUDALLUR; Rugludallur-Logo_SilkScreen
G102: LOGO_ANT; Ant_Logo_SilkScreen
H101, H102, H103, H104: MountingHole; MountingHole_3mm
J101: Conn_02x20_Odd_Even Header; PinSocket_2x20_P2.54mm_Vertical
J102, J103: TBP01R2W-508-16BE; CUI_TBP01R2W-508-16BE
K101, K102, K103, K104, K105, K106, K107, K108, K109, K110, K111, K112, K113, K114, K115, K116: ALFG2PF121
LOGO101: Logo_Open_Hardware_Large; KiCad-Logo2_12mm_SilkScreen
LOGO102: Logo_Open_Hardware_Large; OSHW-Logo2_24.3x20mm_SilkScreen

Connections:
/K1_COIL_ON: J101.1, J101.2, K101.4
/K2_COIL_ON: J101.3, J101.4, K103.4
/K3_COIL_ON: J101.5, J101.6, K105.3
/K4_COIL_ON: J101.7, J101.8, K107.3
/K5_COIL_ON: J101.9, J101.10, K109.4
/K6_COIL_ON: J101.11, J101.12, K111.4
/K7_COIL_ON: J101.13, J101.14, K113.3
/K8_COIL_ON: J101.15, J101.16, K115.3
/K9_COIL_ON: J101.17, J101.18, K116.4
/K10_COIL_ON: J101.19, J101.20, K114.4
/K11_COIL_ON: J101.21, J101.22, K112.4
/K12_COIL_ON: J101.23, J101.24, K110.3
/K13_COIL_ON: J101.25, J101.26, K108.4
/K14_COIL_ON: J101.27, J101.28, K106.4
/K15_COIL_ON: J101.29, J101.30, K104.3
/K16_COIL_ON: J101.31, J101.32, K102.3
GND: J101.33, J101.34, J101.35, J101.36, J101.37, J101.38, J101.39, J101.40, K101.3, K102.4, K103.3, K104.4, K105.4, K106.3, K107.4, K108.3, K109.3, K110.4, K111.3, K112.3, K113.4, K114.3, K115.4, K116.3
unnamed: J102.1, K101.1
unnamed: J102.2, K103.1
unnamed: J102.3, K105.2
unnamed: J102.4, K107.2
unnamed: J102.5, K109.1
unnamed: J102.6, K111.1
unnamed: J102.7, K113.2
unnamed: J102.8, K115.2
unnamed: J102.9, K116.1
unnamed: J102.10, K114.1
unnamed: J102.11, K112.1
unnamed: J102.12, K110.2
unnamed: J102.13, K108.1
unnamed: J102.14, K106.1
unnamed: J102.15, K104.2
unnamed: J102.16, K102.2
unnamed: J103.1, K101.2
unnamed: J103.2, K103.2
unnamed: J103.3, K105.1
unnamed: J103.4, K107.1
unnamed: J103.5, K109.2
unnamed: J103.6, K111.2
unnamed: J103.7, K113.1
unnamed: J103.8, K115.1
unnamed: J103.9, K116.2
unnamed: J103.10, K114.2
unnamed: J103.11, K112.2
unnamed: J103.12, K110.1
unnamed: J103.13, K108.2
unnamed: J103.14, K106.2
unnamed: J103.15, K104.1
unnamed: J103.16, K102.1
